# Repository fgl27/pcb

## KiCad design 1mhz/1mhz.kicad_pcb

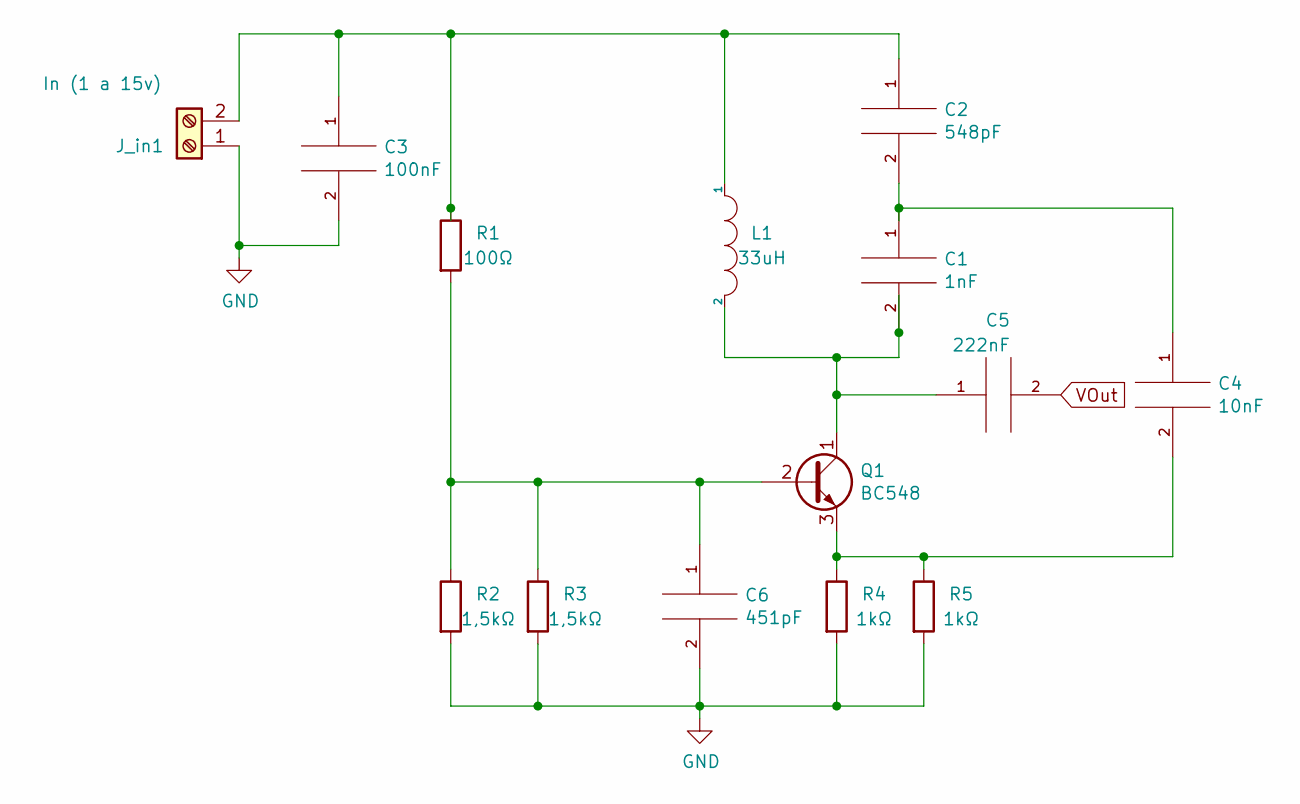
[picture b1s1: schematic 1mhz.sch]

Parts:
C1: 1nF; C_Disc_D3.8mm_W2.6mm_P2.50mm
C2: 548pF; C_Disc_D7.5mm_W5.0mm_P5.00mm
C3: 100nF; C_Disc_D7.5mm_W5.0mm_P5.00mm
C4: 10nF; C_Disc_D6.0mm_W4.4mm_P5.00mm
C5: 222nF; C_Rect_L10.0mm_W3.0mm_P7.50mm_MKS4
C6: 451pF; C_Disc_D7.5mm_W5.0mm_P5.00mm
J_in1: In (1 a 15v); TerminalBlock_Altech_AK300-2_P5.00mm
L1: 33uH; L_Toroid_Vertical_L19.1mm_W8.1mm_P7.10mm_Bourns_5700
Q1: BC548; TO-92_Inline
R1: 100Ω; R_Axial_DIN0207_L6.3mm_D2.5mm_P10.16mm_Horizontal
R2, R3: 1,5kΩ; R_Axial_DIN0207_L6.3mm_D2.5mm_P10.16mm_Horizontal
R4, R5: 1kΩ; R_Axial_DIN0207_L6.3mm_D2.5mm_P10.16mm_Horizontal

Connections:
GND: C3.2, C6.2, J_in1.1, R2.2, R3.2, R4.2, R5.2
unnamed: C2.1, C3.1, J_in1.2, L1.1, R1.1
unnamed: C1.1, C2.2, C4.1
unnamed: C1.2, C5.1, L1.2, Q1.1 (C)
unnamed: C4.2, Q1.3 (E), R4.1, R5.1
unnamed: C6.1, Q1.2 (B), R1.2, R2.1, R3.1
VOut: C5.2

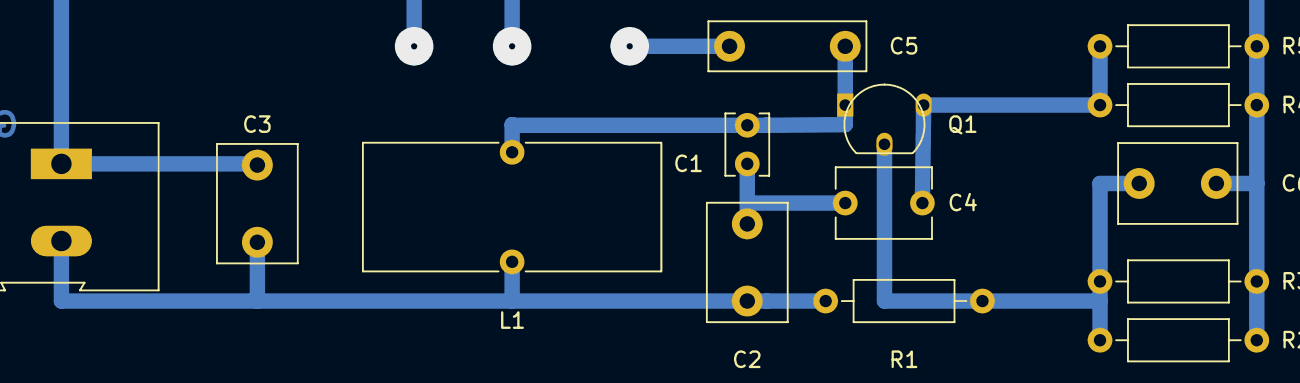
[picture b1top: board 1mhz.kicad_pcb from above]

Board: 2 copper layers, 14 parts (0 on the bottom side), 6 nets.
